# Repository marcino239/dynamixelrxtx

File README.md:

dynamixelrxtx
=============

Interface board USB / serial to Dynamixel serial

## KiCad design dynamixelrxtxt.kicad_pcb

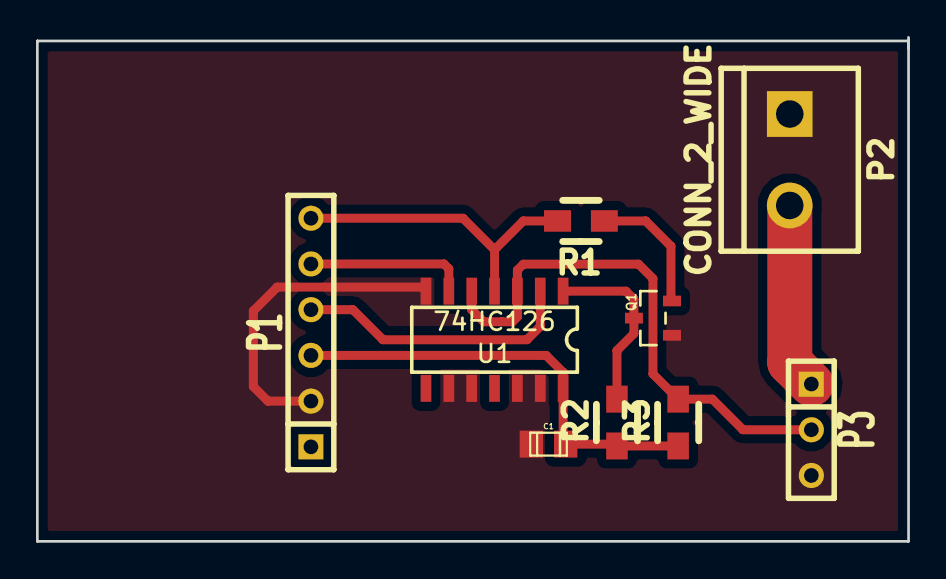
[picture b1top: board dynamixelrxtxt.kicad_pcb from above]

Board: 2 copper layers, 48.4 x 28.0 mm, 9 parts (0 on the bottom side), 9 nets.

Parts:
C1: 100N; c_0805
P1: CONN_6; SIL-6
P2: CONN_2_WIDE; bornier2
P3: CONN_3_WIDE; SIL-3
Q1: BC847; sot23
R1: 22K; Resistor_SMD0805_HandSoldering
R2: 4K7; Resistor_SMD0805_HandSoldering
R3: 10K; Resistor_SMD0805_HandSoldering
U1: 74HC126; SOIC-14_Narrow

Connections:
/DTR: P1.6, R1.2, U1.4
/RXD: P1.5, U1.6
/TXD: P1.4, U1.2
GND: C1.2, P1.2, P2.1, P3.3, Q1.1, U1.7, U1.9, U1.10, U1.12, U1.13
unnamed: P2.2, P3.1
unnamed: P3.2, R3.2, U1.3, U1.5
unnamed: Q1.2, R1.1
unnamed: Q1.3, R2.2, U1.1
VCC: C1.1, P1.3, R2.1, R3.1, U1.14

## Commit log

2014-06-10 initial files
